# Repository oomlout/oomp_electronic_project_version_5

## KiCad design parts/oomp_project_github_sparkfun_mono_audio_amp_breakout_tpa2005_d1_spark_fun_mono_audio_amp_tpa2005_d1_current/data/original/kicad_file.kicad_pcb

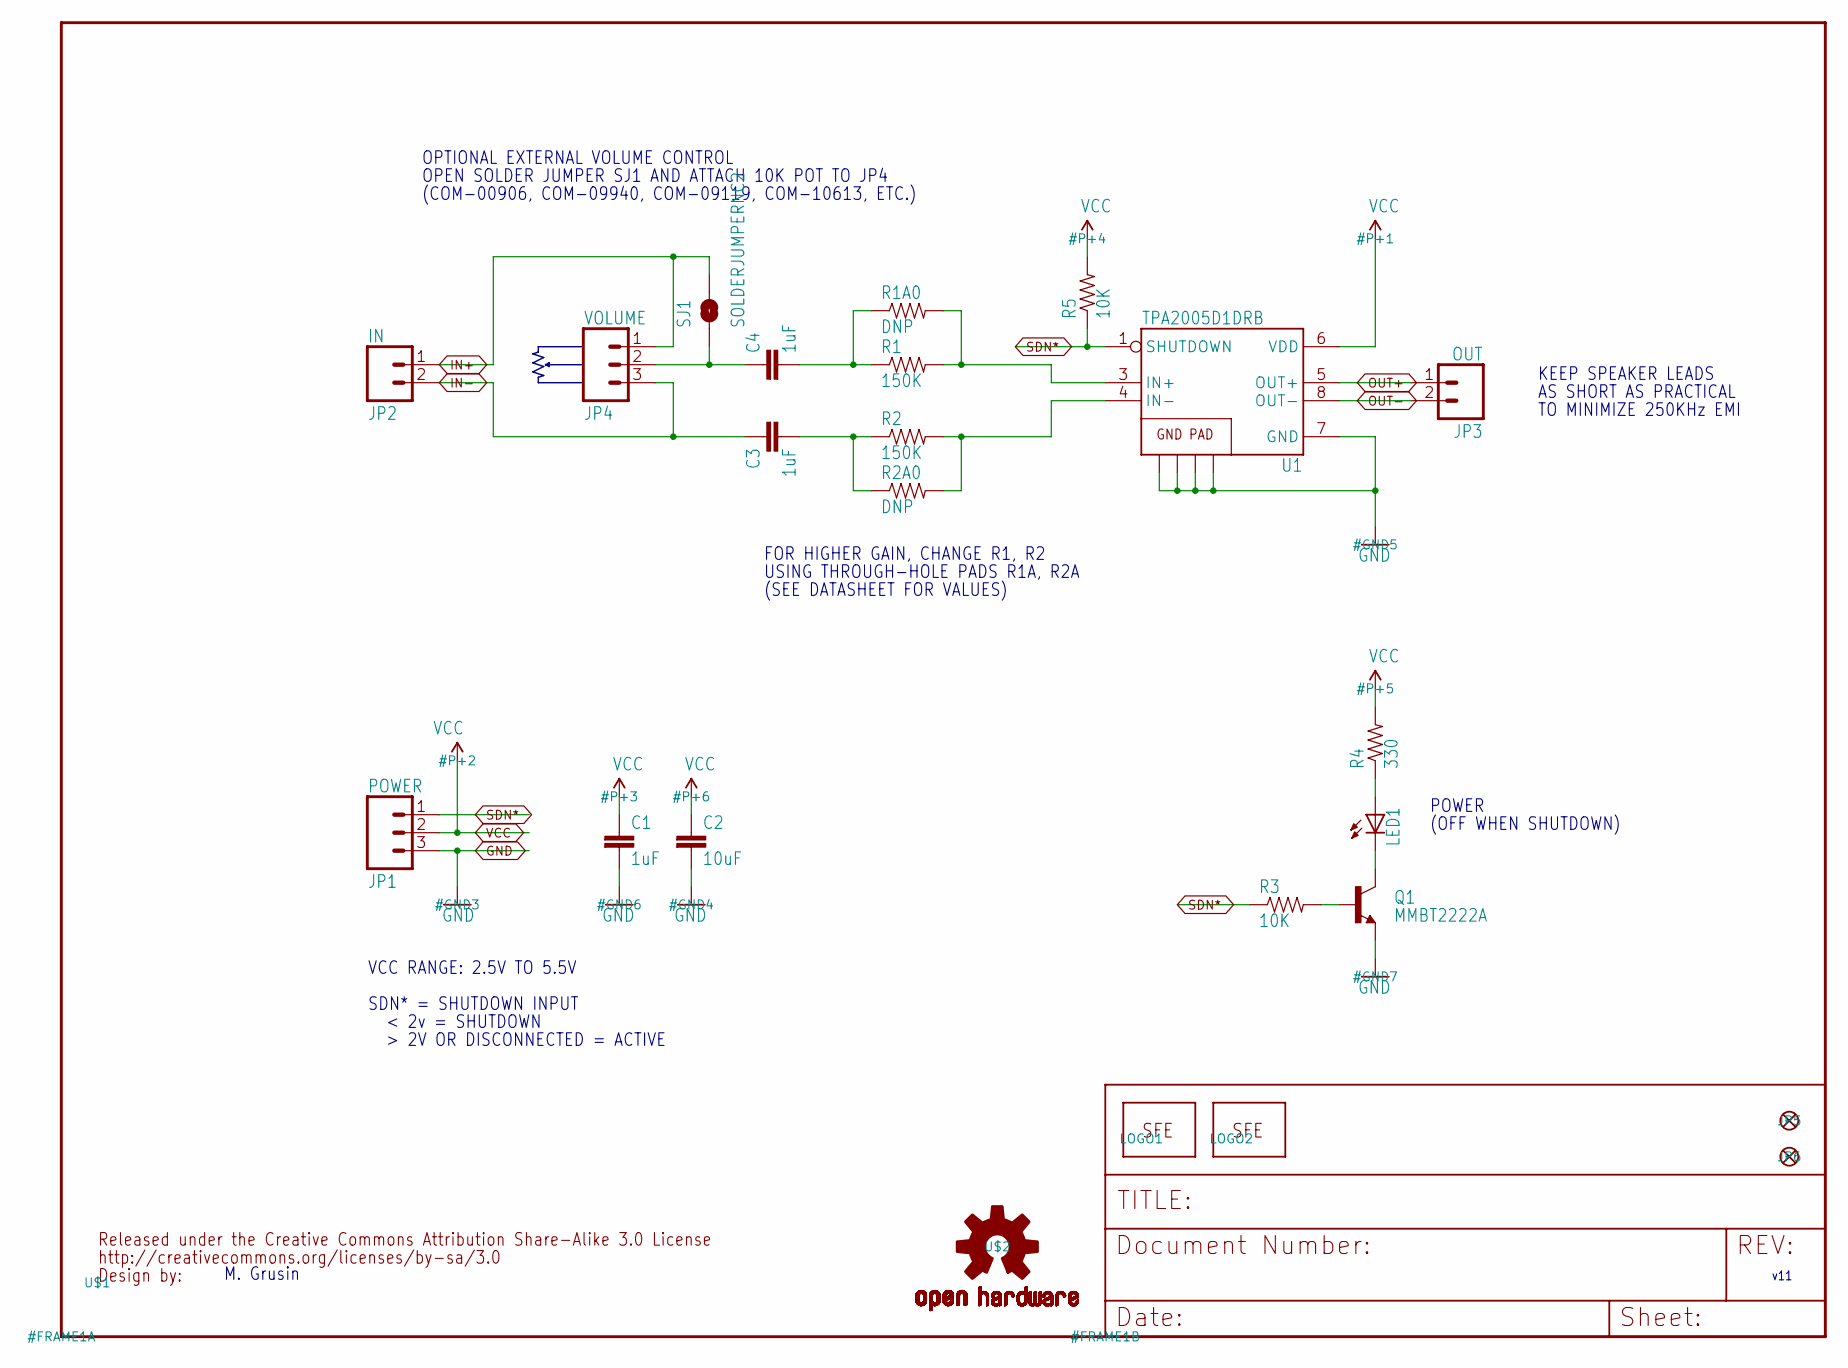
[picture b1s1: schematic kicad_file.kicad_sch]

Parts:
C1, C3, C4: 1uF; 1206
C2: 10uF; 1206
JP1: POWER; 1X03
JP2: IN; 1X02
JP3: OUT; 1X02
JP4: VOLUME; 1X03
JP5, JP6: FIDUCIALUFIDUCIAL; MICRO-FIDUCIAL
LED1: LED0603; LED-0603
LOGO1: LOGO-SFENW2; SFE-NEW-WEB
LOGO2: LOGO-SFESK; SFE-LOGO-FLAME
Q1: MMBT2222A; SOT23-3
R1, R2: 150K; 0603-RES
R1A0, R2A0: DNP; AXIAL-0.3
R3, R5: 10K; 0603-RES
R4: 330; 0603-RES
SJ1: SOLDERJUMPERNC2; SJ_2S-NOTRACE
U1: TPA2005D1DRB; QFN-8_PAD
U$1: CREATIVE_COMMONS
U$2: OSHW-LOGOS; OSHW-LOGO-S

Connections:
GND: C1.2, C2.2, JP1.3, Q1.2 (E), U1.7 (GND), U1.10 (GND), U1.11 (GND), U1.12 (GND), U1.13 (GND)
IN+: JP2.1, JP4.1, SJ1.2
IN+AMP: R1.2, R1A0.P$2 (2), U1.3 (IN+)
IN-: C3.1, JP2.2, JP4.3
IN-AMP: R2.2, R2A0.P$2 (2), U1.4 (IN-)
unnamed: C4.1, JP4.2, SJ1.1
unnamed: C4.2, R1.1, R1A0.P$1 (1)
unnamed: C3.2, R2.1, R2A0.P$1 (1)
unnamed: LED1.C, Q1.3 (C)
unnamed: LED1.A, R4.1
unnamed: Q1.1 (B), R3.2
OUT+: JP3.1, U1.5 (OUT+)
OUT-: JP3.2, U1.8 (OUT-)
SDN*: JP1.1, R3.1, R5.1, U1.1 (SHUTDOWN)
VCC: C1.1, C2.1, JP1.2, R4.2, R5.2, U1.6 (VDD)

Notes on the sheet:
TO MINIMIZE 250KHz EMI
KEEP SPEAKER LEADS
FOR HIGHER GAIN, CHANGE R1, R2
(OFF WHEN SHUTDOWN)
M. Grusin
OPTIONAL EXTERNAL VOLUME CONTROL
USING THROUGH-HOLE PADS R1A, R2A
SDN* = SHUTDOWN INPUT
VCC RANGE: 2.5V TO 5.5V
POWER
OPEN SOLDER JUMPER SJ1 AND ATTACH 10K POT TO JP4
< 2v = SHUTDOWN
(COM-00906, COM-09940, COM-09119, COM-10613, ETC.)
v11
(SEE DATASHEET FOR VALUES)
> 2V OR DISCONNECTED = ACTIVE
AS SHORT AS PRACTICAL

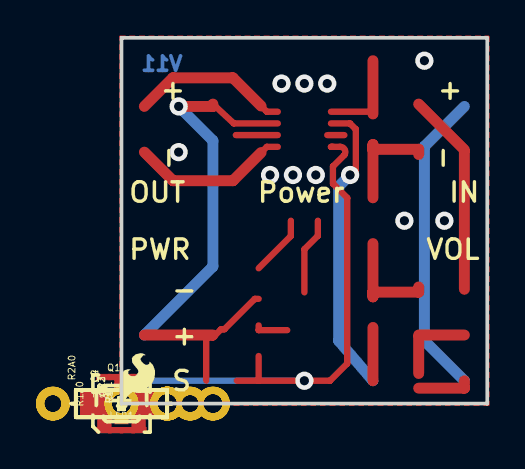
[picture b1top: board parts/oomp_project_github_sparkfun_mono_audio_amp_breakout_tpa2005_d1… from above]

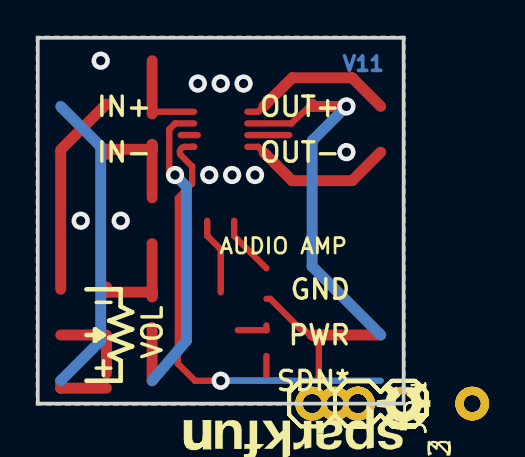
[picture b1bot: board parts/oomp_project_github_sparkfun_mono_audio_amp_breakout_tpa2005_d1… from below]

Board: 2 copper layers, 20.3 x 20.3 mm, 25 parts (6 on the bottom side), 15 nets.

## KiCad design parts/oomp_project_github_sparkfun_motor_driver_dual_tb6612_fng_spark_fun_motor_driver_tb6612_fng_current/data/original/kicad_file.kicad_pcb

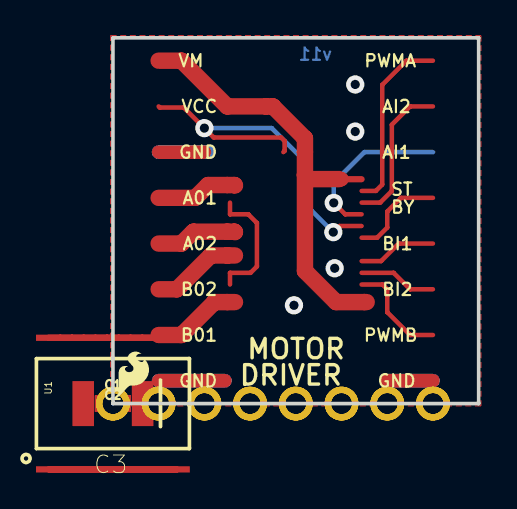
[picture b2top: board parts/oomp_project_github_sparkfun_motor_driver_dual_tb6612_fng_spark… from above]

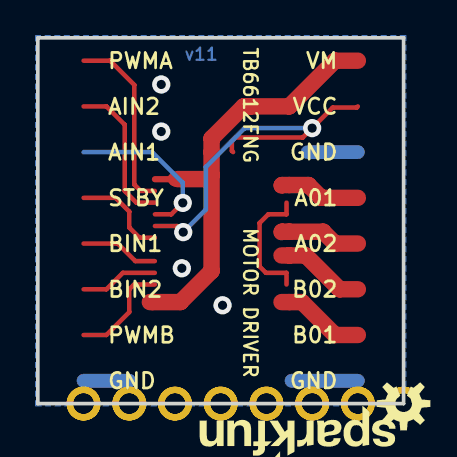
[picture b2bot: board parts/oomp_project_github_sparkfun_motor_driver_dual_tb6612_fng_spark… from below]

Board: 16 copper layers, 20.3 x 20.3 mm, 14 parts (4 on the bottom side), 14 nets.

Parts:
C1, C2: 0.1uF; 0402
C3: 10uF; EIA3528
FD1, FD2, FD3, FD4: FIDUCIALUFIDUCIAL; FIDUCIAL-MICRO
FRAME1: FRAME-LETTER; CREATIVE_COMMONS
JP1, JP2: 1X08_OFFSET_REDUCED
LOGO1: SFE_LOGO_FLAME.1_INCH; SFE_LOGO_FLAME_.1
LOGO2: OSHW-LOGOS; OSHW-LOGO-S
LOGO4: SFE_LOGO_NAME_FLAME.1_INCH; SFE_LOGO_NAME_FLAME_.1
U1: TB6612FNG; SSOP24

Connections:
A01: JP1.5, U1.1, U1.2
A02: JP1.4, U1.5, U1.6
AIN1: JP2.3, U1.21
AIN2: JP2.2, U1.22
B01: JP1.2, U1.11, U1.12
B02: JP1.3, U1.7, U1.8
BIN1: JP2.5, U1.17
BIN2: JP2.6, U1.16
GND: C1.2, C2.2, C3.C, JP1.1, JP1.6, JP2.8, U1.3, U1.4, U1.9, U1.10, U1.18
PWMA: JP2.1, U1.23
PWMB: JP2.7, U1.15
STBY: JP2.4, U1.19
VCC: C2.1, JP1.7, U1.20
VM: C1.1, C3.A, JP1.8, U1.13, U1.14, U1.24

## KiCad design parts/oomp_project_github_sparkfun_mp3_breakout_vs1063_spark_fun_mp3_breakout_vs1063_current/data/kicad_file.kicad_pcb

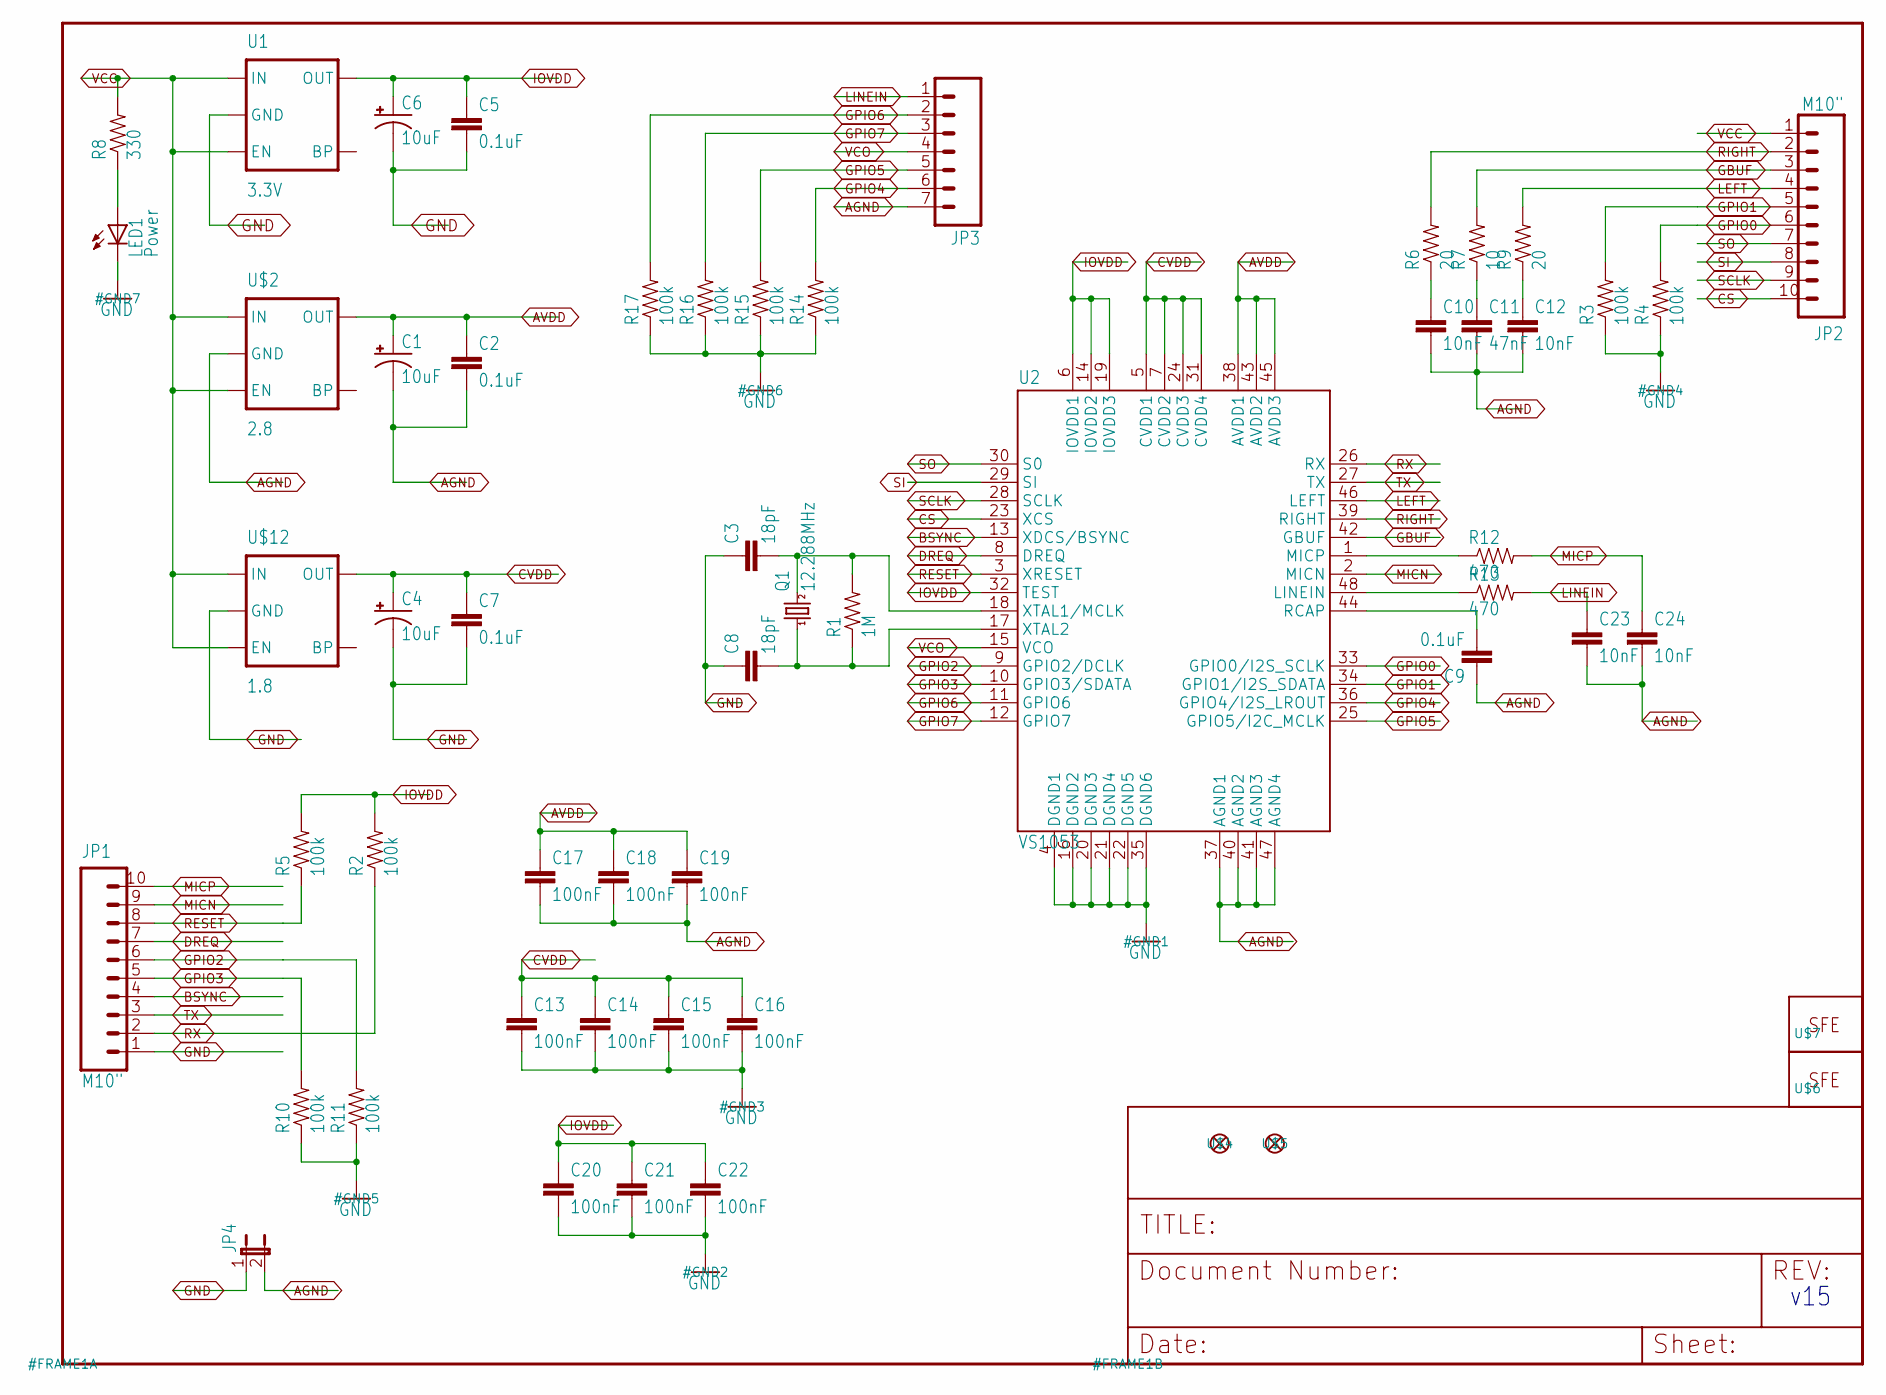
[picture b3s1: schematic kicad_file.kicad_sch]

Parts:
C1, C4, C6: 10uF; EIA3216
C2, C5, C7, C9: 0.1uF; 0402-CAP
C3, C8: 18pF; 0402-CAP
C10, C12, C23, C24: 10nF; 0402-CAP
C11: 47nF; 0402-CAP
C13, C14, C15, C16, C17, C18, C19, C20, C21, C22: 100nF; 0402-CAP
JP1, JP2: M10"; 1X10
JP3: M07; 1X07
JP4: JUMPER-2SMD-NC; SJ_2S
LED1: Power; LED-0603
Q1: 12.288MHz; CRYSTAL-SMD-5X3
R1: 1M; 0402-RES
R2, R3, R4, R5, R10, R11, R14, R15, R16, R17: 100k; 0402-RES
R6, R9: 20; 0402-RES
R7: 10; 0402-RES
R8: 330; 0402-RES
R12, R13: 470; 0402-RES
U1: 3.3V; SOT23-5
U2: VS1053; LQFP-48
U$2: 2.8; SC70
U$4, U$5: FIDUCIAL1X2; FIDUCIAL-1X2
U$6: LOGO-SFESK; SFE-LOGO-FLAME
U$7: LOGO-SFENEW; SFE-NEW-WEBLOGO
U$12: 1.8; SC70

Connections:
AGND: C1.C (-), C2.2, C9.1, C10.2, C11.2, C12.2, C17.2, C18.2, C19.2, C23.2, C24.2, JP3.7, JP4.2, U2.37 (AGND1), U2.40 (AGND2), U2.41 (AGND3), U2.47 (AGND4), U$2.2 (GND)
AVDD: C1.A (+), C2.1, C17.1, C18.1, C19.1, U2.38 (AVDD1), U2.43 (AVDD2), U2.45 (AVDD3), U$2.5 (OUT)
BSYNC: JP1.4, U2.13 (XDCS/BSYNC)
CS: JP2.10, U2.23 (XCS)
CVDD: C4.A (+), C7.1, C13.1, C14.1, C15.1, C16.1, U2.5 (CVDD1), U2.7 (CVDD2), U2.24 (CVDD3), U2.31 (CVDD4), U$12.5 (OUT)
DREQ: JP1.7, U2.8 (DREQ)
GBUF: JP2.3, R7.2, U2.42 (GBUF)
GND: C3.1, C4.C (-), C5.2, C6.C (-), C7.2, C8.1, C13.2, C14.2, C15.2, C16.2, C20.2, C21.2, C22.2, JP1.1, JP4.1, LED1.C, R3.1, R4.1, R10.1, R11.1, R14.1, R15.1, R16.1, R17.1, U1.2 (GND), U2.4 (DGND1), U2.16 (DGND2), U2.20 (DGND3), U2.21 (DGND4), U2.22 (DGND5), U2.35 (DGND6), U$12.2 (GND)
GPIO0: JP2.6, R4.2, U2.33 (GPIO0/I2S_SCLK)
GPIO1: JP2.5, R3.2, U2.34 (GPIO1/I2S_SDATA)
GPIO2: JP1.6, R11.2, U2.9 (GPIO2/DCLK)
GPIO3: JP1.5, R10.2, U2.10 (GPIO3/SDATA)
GPIO4: JP3.6, R14.2, U2.36 (GPIO4/I2S_LROUT)
GPIO5: JP3.5, R15.2, U2.25 (GPIO5/I2C_MCLK)
GPIO6: JP3.2, R17.2, U2.11 (GPIO6)
GPIO7: JP3.3, R16.2, U2.12 (GPIO7)
IOVDD: C5.1, C6.A (+), C20.1, C21.1, C22.1, R2.2, R5.2, U1.5 (OUT), U2.6 (IOVDD1), U2.14 (IOVDD2), U2.19 (IOVDD3), U2.32 (TEST)
LEFT: JP2.4, R9.2, U2.46 (LEFT)
LINEIN: C23.1, JP3.1, R13.2
MICN: JP1.9, U2.2 (MICN)
MICP: C24.1, JP1.10, R12.2
unnamed: C9.2, U2.44 (RCAP)
unnamed: C12.1, R9.1
unnamed: C10.1, R6.1
unnamed: R12.1, U2.1 (MICP)
unnamed: C11.1, R7.1
unnamed: LED1.A, R8.1
unnamed: R13.1, U2.48 (LINEIN)
unnamed: C3.2, Q1.3 (2), R1.2, U2.18 (XTAL1/MCLK)
unnamed: C8.2, Q1.1, R1.1, U2.17 (XTAL2)
RESET: JP1.8, R5.1, U2.3 (XRESET)
RIGHT: JP2.2, R6.2, U2.39 (RIGHT)
RX: JP1.2, R2.1, U2.26 (RX)
SCLK: JP2.9, U2.28 (SCLK)
SI: JP2.8, U2.29 (SI)
SO: JP2.7, U2.30 (S0)
TX: JP1.3, U2.27 (TX)
VCC: JP2.1, R8.2, U1.1 (IN), U1.3 (EN), U$2.1 (IN), U$2.3 (EN), U$12.1 (IN), U$12.3 (EN)
VCO: JP3.4, U2.15 (VCO)

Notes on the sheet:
v15

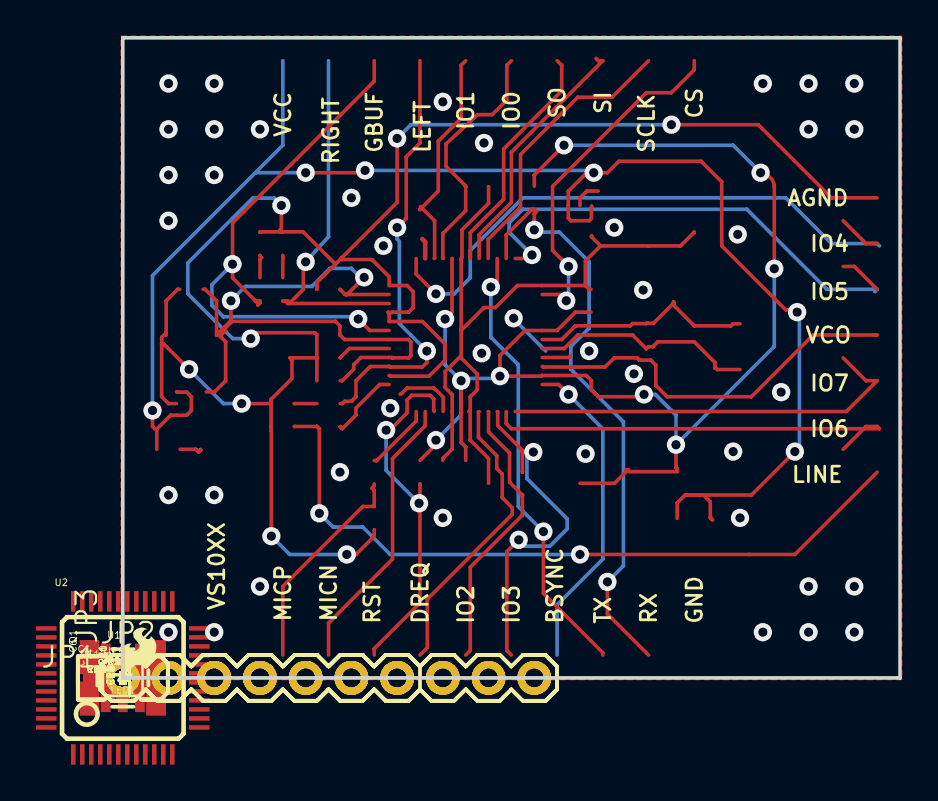
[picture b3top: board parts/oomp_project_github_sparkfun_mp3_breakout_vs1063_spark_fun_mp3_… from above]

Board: 2 copper layers, 43.2 x 35.6 mm, 55 parts (1 on the bottom side), 39 nets.

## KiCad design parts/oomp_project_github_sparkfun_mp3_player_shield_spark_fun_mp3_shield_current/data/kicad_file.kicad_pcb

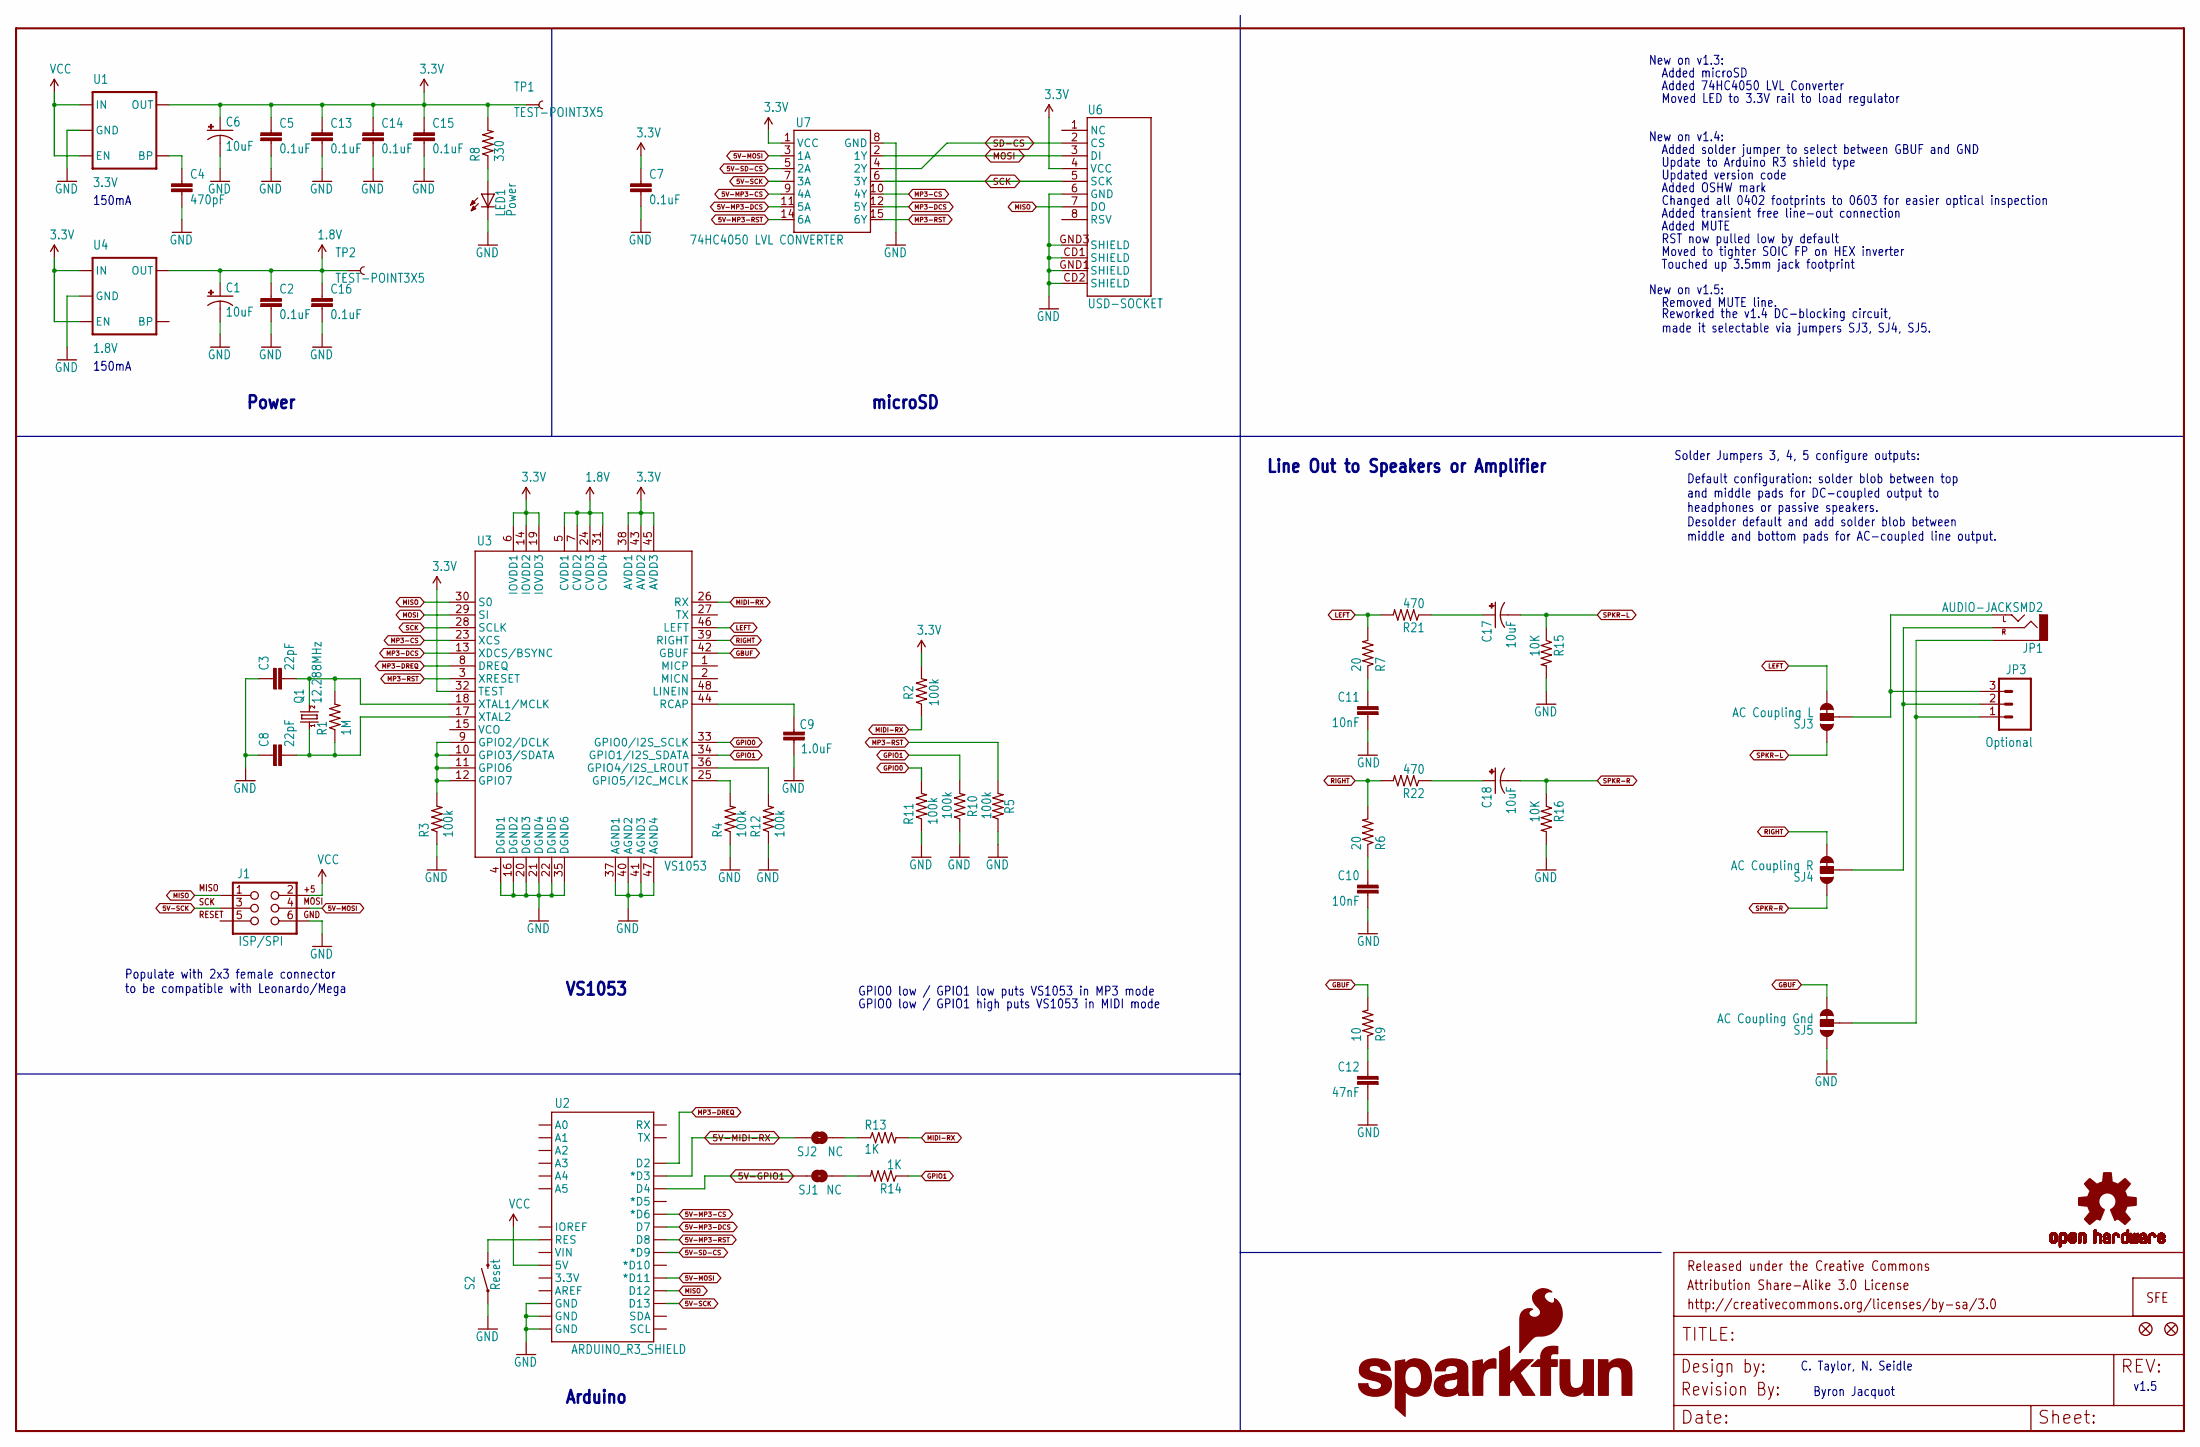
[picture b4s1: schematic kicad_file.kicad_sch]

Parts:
C1, C6, C17, C18: 10uF; EIA3216
C2, C5, C7, C13, C14, C15, C16: 0.1uF; 0603-CAP
C3, C8: 22pF; 0603-CAP
C4: 470pF; 0603-CAP
C9: 1.0uF; 0603-CAP
C10, C11: 10nF; 0603-CAP
C12: 47nF; 0603-CAP
FRAME1: FRAME-LEDGER; CREATIVE_COMMONS
J1: ISP/SPI; 2X3
JP1: AUDIO-JACKSMD2; AUDIO-JACK-3.5MM-SMD
JP3: Optional; 1X03
LED1: Power; LED-0603
LOGO1: OSHW-LOGOS; OSHW-LOGO-S
LOGO2: SFE_LOGO_NAME_FLAME.1_INCH; SFE_LOGO_NAME_FLAME_.1
Q1: 12.288MHz; CRYSTAL-SMD-5X3
R1: 1M; 0603-RES
R2, R3, R4, R5, R10, R11, R12: 100k; 0603-RES
R6, R7: 20; 0603-RES
R8: 330; 0603-RES
R9: 10; 0603-RES
R13, R14: 1K; 0603-RES
R15, R16: 10K; 0603-RES
R21, R22: 470; 0603-RES
S2: Reset; TACTILE_SWITCH_SMD
SJ1, SJ2: NC; SJ_2S-TRACE
SJ3: AC Coupling L; SMT-JUMPER_3_1-NC_TRACE_SILK
SJ4: AC Coupling R; SMT-JUMPER_3_1-NC_TRACE_SILK
SJ5: AC Coupling Gnd; SMT-JUMPER_3_1-NC_TRACE_SILK
TP1, TP2: TEST-POINT3X5; PAD.03X.05
U1: 3.3V; SOT23-5
U2: ARDUINO_R3_SHIELD; UNO_R3_SHIELD
U3: VS1053; LQFP-48
U4: 1.8V; SC70
U6: USD-SOCKET; MICRO-SD-SOCKET-PP
U7: 74HC4050 LVL CONVERTER; SO016
U$1: REVISION
U$4, U$5: FIDUCIAL1X2; FIDUCIAL-1X2
U$8: LOGO-SFENEW; SFE-NEW-WEBLOGO

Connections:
1.8V: C1.A (+), C2.1, C16.1, TP2.P$1, U3.5 (CVDD1), U3.7 (CVDD2), U3.24 (CVDD3), U3.31 (CVDD4), U4.5 (OUT)
3.3V: C5.1, C6.A (+), C7.1, C13.1, C14.1, C15.1, R2.2, R8.2, TP1.P$1, U1.5 (OUT), U3.6 (IOVDD1), U3.14 (IOVDD2), U3.19 (IOVDD3), U3.32 (TEST), U3.38 (AVDD1), U3.43 (AVDD2), U3.45 (AVDD3), U4.1 (IN), U4.3 (EN), U6.4 (VCC), U7.1 (VCC)
5V-GPIO1: SJ1.2, U2.D4
5V-MIDI-RX: SJ2.1, U2.D3 (*D3)
5V-MOSI: J1.4, U2.D11 (*D11), U7.3 (1A)
5V-MP3-CS: U2.D6 (*D6), U7.9 (4A)
5V-MP3-DCS: U2.D7, U7.11 (5A)
5V-MP3-RST: U2.D8, U7.14 (6A)
5V-SCK: J1.3, U2.D13, U7.7 (3A)
5V-SD-CS: U2.D9 (*D9), U7.5 (2A)
ARST: S2.3 (2), U2.RES
G1: R3.2, U3.9 (GPIO2/DCLK), U3.10 (GPIO3/SDATA), U3.11 (GPIO6), U3.12 (GPIO7)
G2: R4.2, U3.25 (GPIO5/I2C_MCLK)
GBUF: R9.2, SJ5.3, U3.42 (GBUF)
GND: C1.C (-), C2.2, C3.1, C4.2, C5.2, C6.C (-), C7.2, C8.1, C9.1, C10.2, C11.2, C12.2, C13.2, C14.2, C15.2, C16.2, J1.6, LED1.C, R3.1, R4.1, R5.1, R10.1, R11.1, R12.1, R15.2, R16.2, S2.1, SJ5.1, U1.2 (GND), U2.GND@0 (GND), U2.GND@1 (GND), U2.GND@2 (GND), U3.4 (DGND1), U3.16 (DGND2), U3.20 (DGND3), U3.21 (DGND4), U3.22 (DGND5), U3.35 (DGND6), U3.37 (AGND1), U3.40 (AGND2), U3.41 (AGND3), U3.47 (AGND4), U4.2 (GND), U6.6 (GND), U6.CD1 (SHIELD), U6.CD2 (SHIELD), U6.GND1 (SHIELD), U6.GND3 (SHIELD), U7.8 (GND)
GPIO0: R11.2, U3.33 (GPIO0/I2S_SCLK)
GPIO1: R10.2, R14.1, U3.34 (GPIO1/I2S_SDATA)
GPIO4: R12.2, U3.36 (GPIO4/I2S_LROUT)
LEFT: R7.2, R21.2, SJ3.3, U3.46 (LEFT)
MIDI-RX: R2.1, R13.2, U3.26 (RX)
MISO: J1.1, U2.D12, U3.30 (S0), U6.7 (DO)
MOSI: U3.29 (SI), U6.3 (DI), U7.2 (1Y)
MP3-CS: U3.23 (XCS), U7.10 (4Y)
MP3-DCS: U3.13 (XDCS/BSYNC), U7.12 (5Y)
MP3-DREQ: U2.D2, U3.8 (DREQ)
MP3-RST: R5.2, U3.3 (XRESET), U7.15 (6Y)
unnamed: C12.1, R9.1
unnamed: C10.1, R6.1
unnamed: R14.2, SJ1.1
unnamed: C11.1, R7.1
unnamed: LED1.A, R8.1
unnamed: R13.1, SJ2.2
unnamed: C3.2, Q1.3 (2), R1.2, U3.18 (XTAL1/MCLK)
unnamed: C8.2, Q1.1, R1.1, U3.17 (XTAL2)
unnamed: JP1.SLEEVE, JP3.1, SJ5.2
unnamed: JP1.RING (RIGHT), JP3.2, SJ4.2
unnamed: JP1.TIP (LEFT), JP3.3, SJ3.2
unnamed: C18.A (+), R22.1
unnamed: C17.A (+), R21.1
unnamed: C4.1, U1.4 (BP)
RCAP: C9.2, U3.44 (RCAP)
RIGHT: R6.2, R22.2, SJ4.3, U3.39 (RIGHT)
SCK: U3.28 (SCLK), U6.5 (SCK), U7.6 (3Y)
SD-CS: U6.2 (CS), U7.4 (2Y)
SPKR-L: C17.C (-), R15.1, SJ3.1
SPKR-R: C18.C (-), R16.1, SJ4.1
VCC: J1.2, U1.1 (IN), U1.3 (EN), U2.5V

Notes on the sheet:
Update to Arduino R3 shield type
Touched up 3.5mm jack footprint
Added transient free line-out connection
v1.5
Added MUTE
C. Taylor, N. Seidle
Updated version code
microSD
New on v1.3:
Populate with 2x3 female connector to be compatible with Leonardo/Mega
New on v1.5:
Byron Jacquot
Added solder jumper to select between GBUF and GND
150mA
Line Out to Speakers or Amplifier
GPIO0 low / GPIO1 high puts VS1053 in MIDI mode
Added microSD
Power
Default configuration: solder blob between top and middle pads for DC-coupled output to headphones or passive speakers. Desolder default and add solder blob between middle and bottom pads for AC-coupled line output.
Arduino
Moved LED to 3.3V rail to load regulator
Added 74HC4050 LVL Converter
Added OSHW mark
VS1053
Removed MUTE line.
Changed all 0402 footprints to 0603 for easier optical inspection
GPIO0 low / GPIO1 low puts VS1053 in MP3 mode
Solder Jumpers 3, 4, 5 configure outputs:
Reworked the v1.4 DC-blocking circuit, made it selectable via jumpers SJ3, SJ4, SJ5.
Moved to tighter SOIC FP on HEX inverter
New on v1.4:
RST now pulled low by default

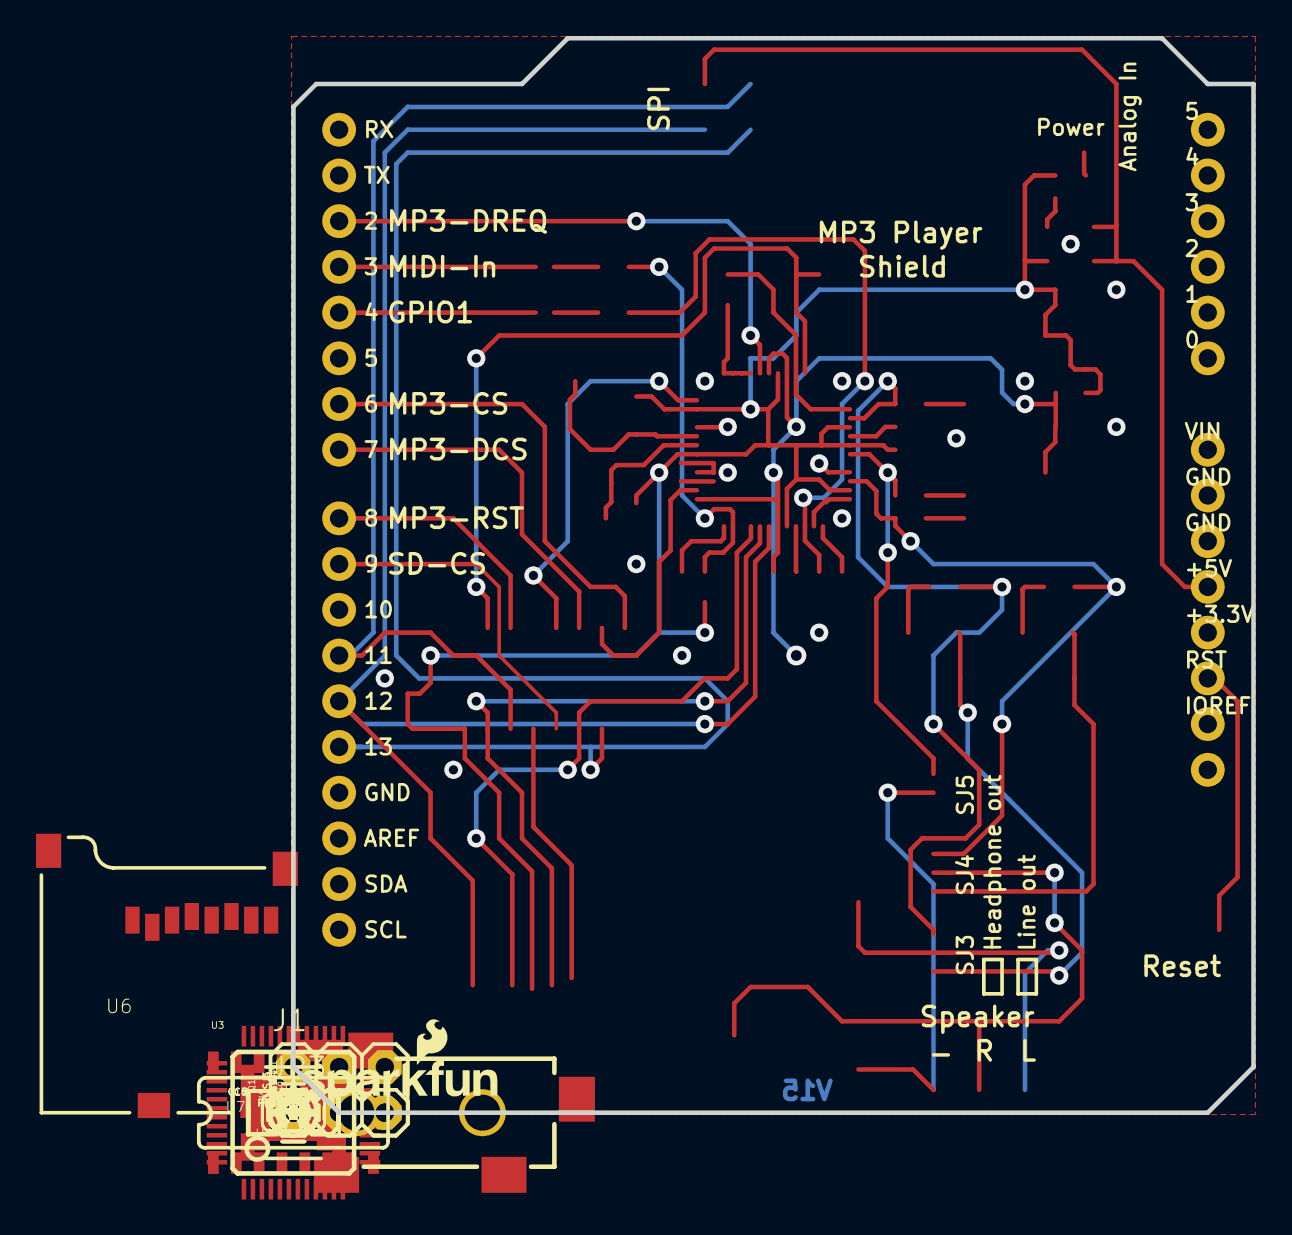
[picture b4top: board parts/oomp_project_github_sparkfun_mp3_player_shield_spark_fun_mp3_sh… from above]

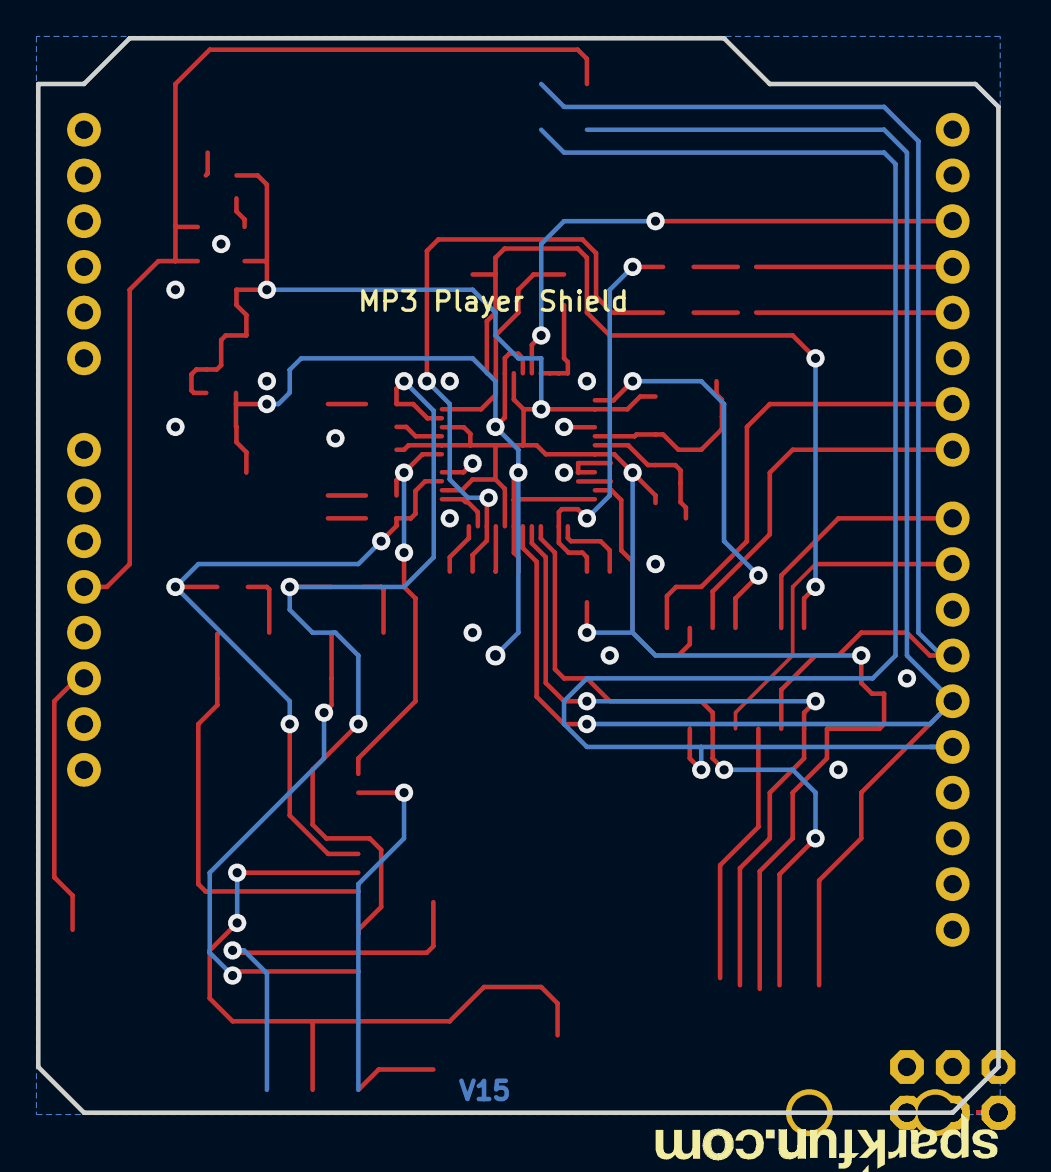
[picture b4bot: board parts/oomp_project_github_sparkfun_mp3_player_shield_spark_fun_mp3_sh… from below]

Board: 2 copper layers, 53.3 x 59.7 mm, 62 parts (3 on the bottom side), 47 nets.

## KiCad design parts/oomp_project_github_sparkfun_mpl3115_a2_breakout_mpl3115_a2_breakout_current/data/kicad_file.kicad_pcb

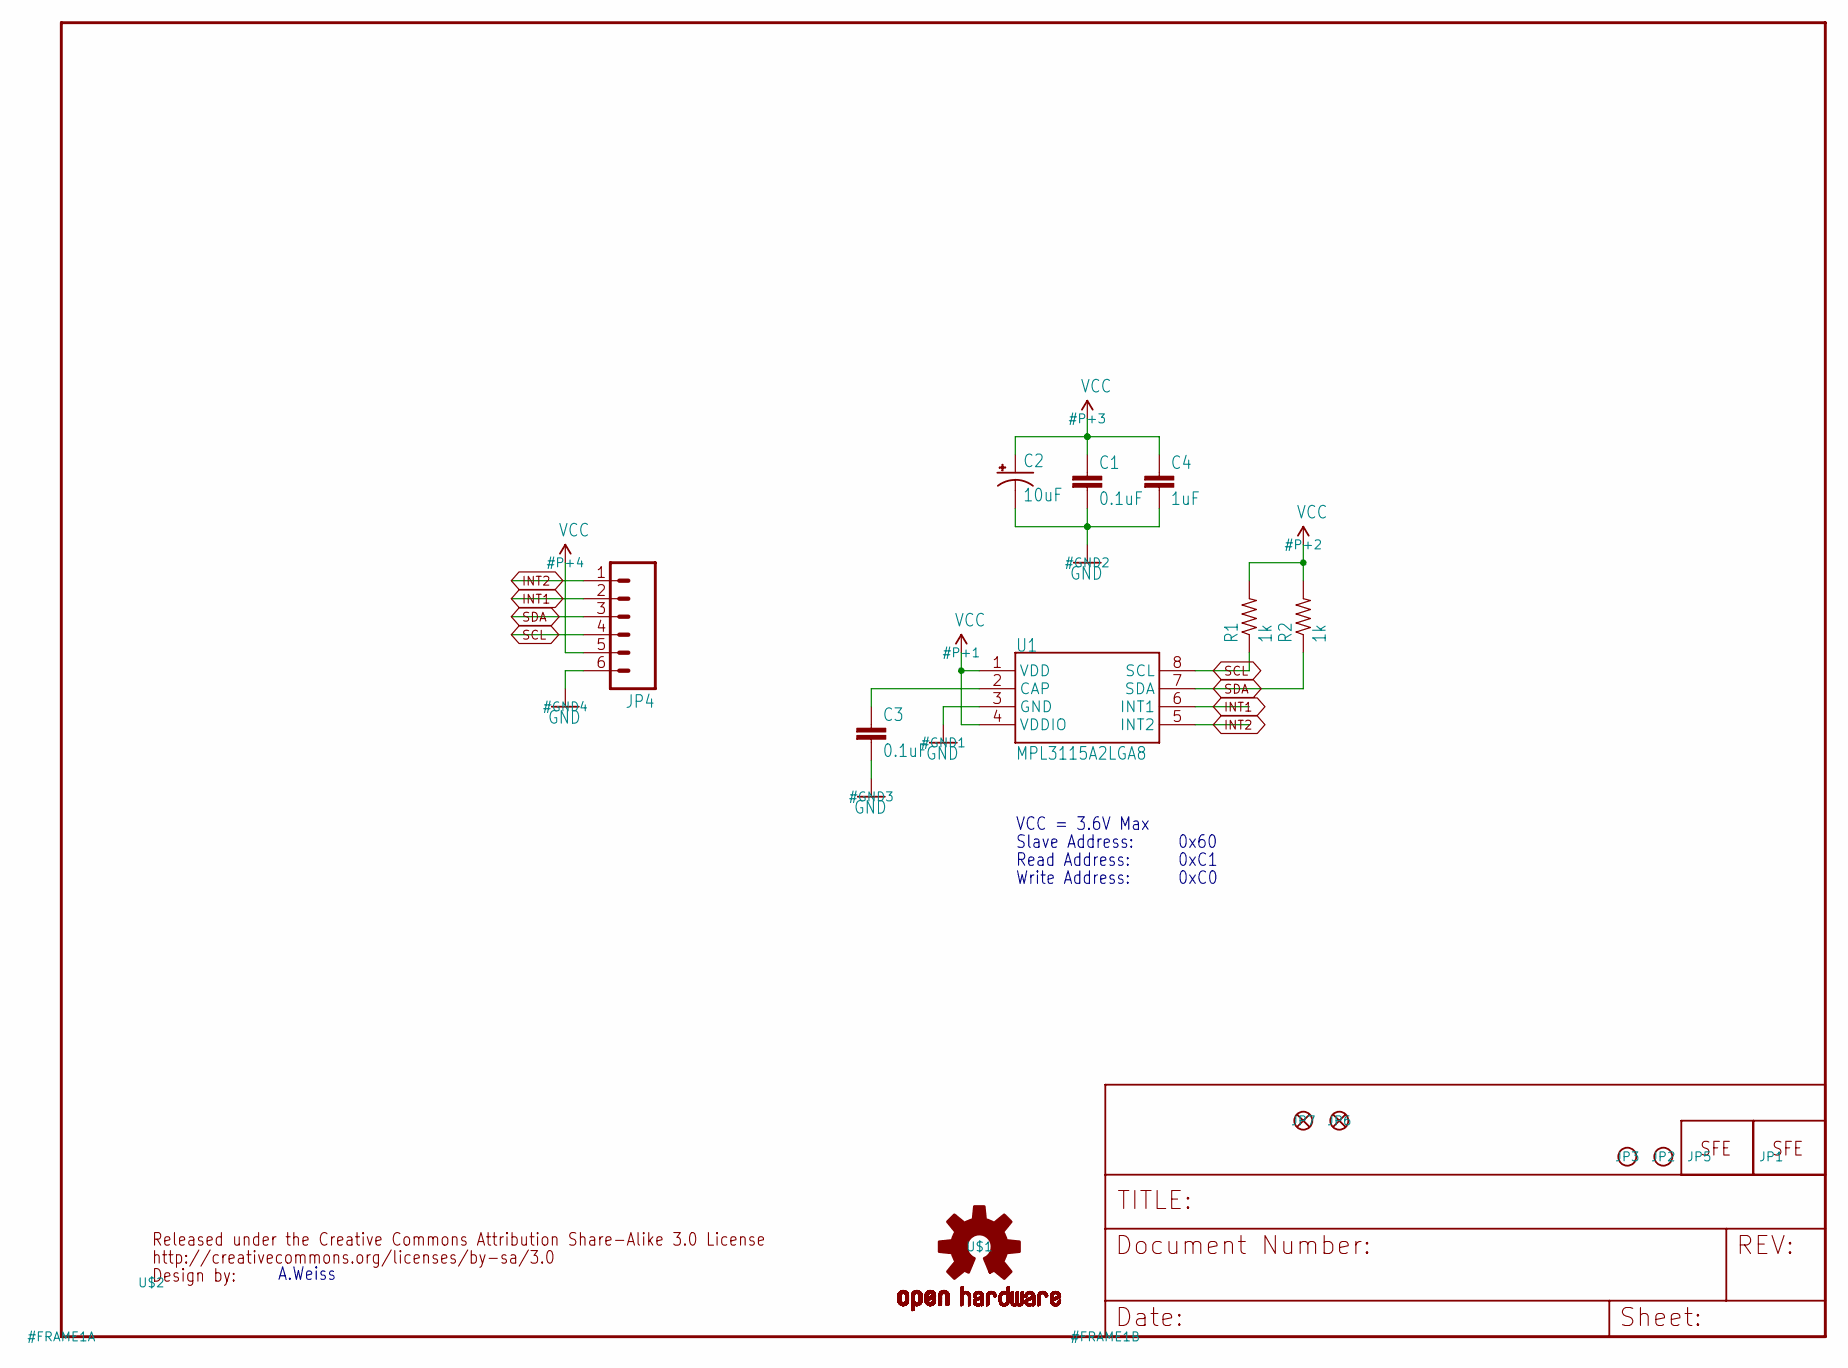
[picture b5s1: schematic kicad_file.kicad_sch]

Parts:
C1, C3: 0.1uF; 0402-CAP
C2: 10uF; EIA3216
C4: 1uF; 0402-CAP
JP1, JP5: LOGO-SFESK; SFE-LOGO-FLAME
JP2, JP3: STAND-OFF
JP4: M06SIP; 1X06
JP6, JP7: FIDUCIALUFIDUCIAL; MICRO-FIDUCIAL
R1, R2: 1k; 0402-RES
U1: MPL3115A2LGA8; LGA8
U$1: OSHW-LOGOS; OSHW-LOGO-S
U$2: CREATIVE_COMMONS

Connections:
GND: C1.2, C2.C (-), C3.2, C4.2, JP4.6, U1.3 (GND)
INT1: JP4.2, U1.6 (INT1)
INT2: JP4.1, U1.5 (INT2)
unnamed: C3.1, U1.2 (CAP)
SCL: JP4.4, R1.1, U1.8 (SCL)
SDA: JP4.3, R2.1, U1.7 (SDA)
VCC: C1.1, C2.A (+), C4.1, JP4.5, R1.2, R2.2, U1.1 (VDD), U1.4 (VDDIO)

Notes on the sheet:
0xC0
VCC = 3.6V Max
A.Weiss
Slave Address:
0x60
Read Address:
0xC1
Write Address:

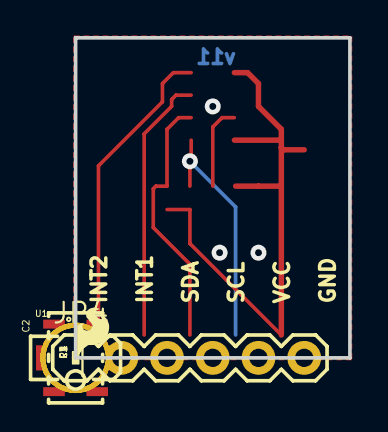
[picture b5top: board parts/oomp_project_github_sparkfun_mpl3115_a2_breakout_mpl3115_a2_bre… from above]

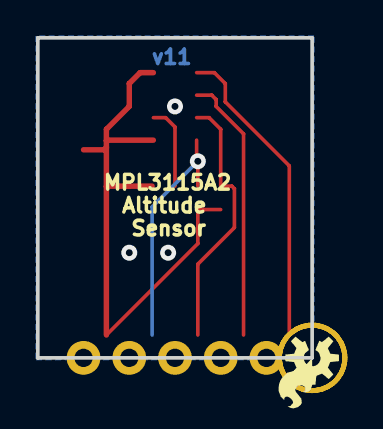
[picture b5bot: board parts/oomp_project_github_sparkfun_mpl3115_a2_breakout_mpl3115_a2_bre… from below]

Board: 2 copper layers, 15.2 x 17.8 mm, 16 parts (2 on the bottom side), 7 nets.

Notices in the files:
parts/oomp_project_github_sparkfun_mono_audio_amp_breakout_tpa2005_d1_spark_fun_mono_audio_amp_tpa2005_d1_current/data/original/kicad_file.kicad_sch:
Released under the Creative Commons Attribution Share-Alike 3.0 License
http://creativecommons.org/licenses/by-sa/3.0
parts and their libraries:
Released under the Creative Commons Attribution Share-Alike 4.0 License
https://creativecommons.org/licenses/by-sa/4.0
